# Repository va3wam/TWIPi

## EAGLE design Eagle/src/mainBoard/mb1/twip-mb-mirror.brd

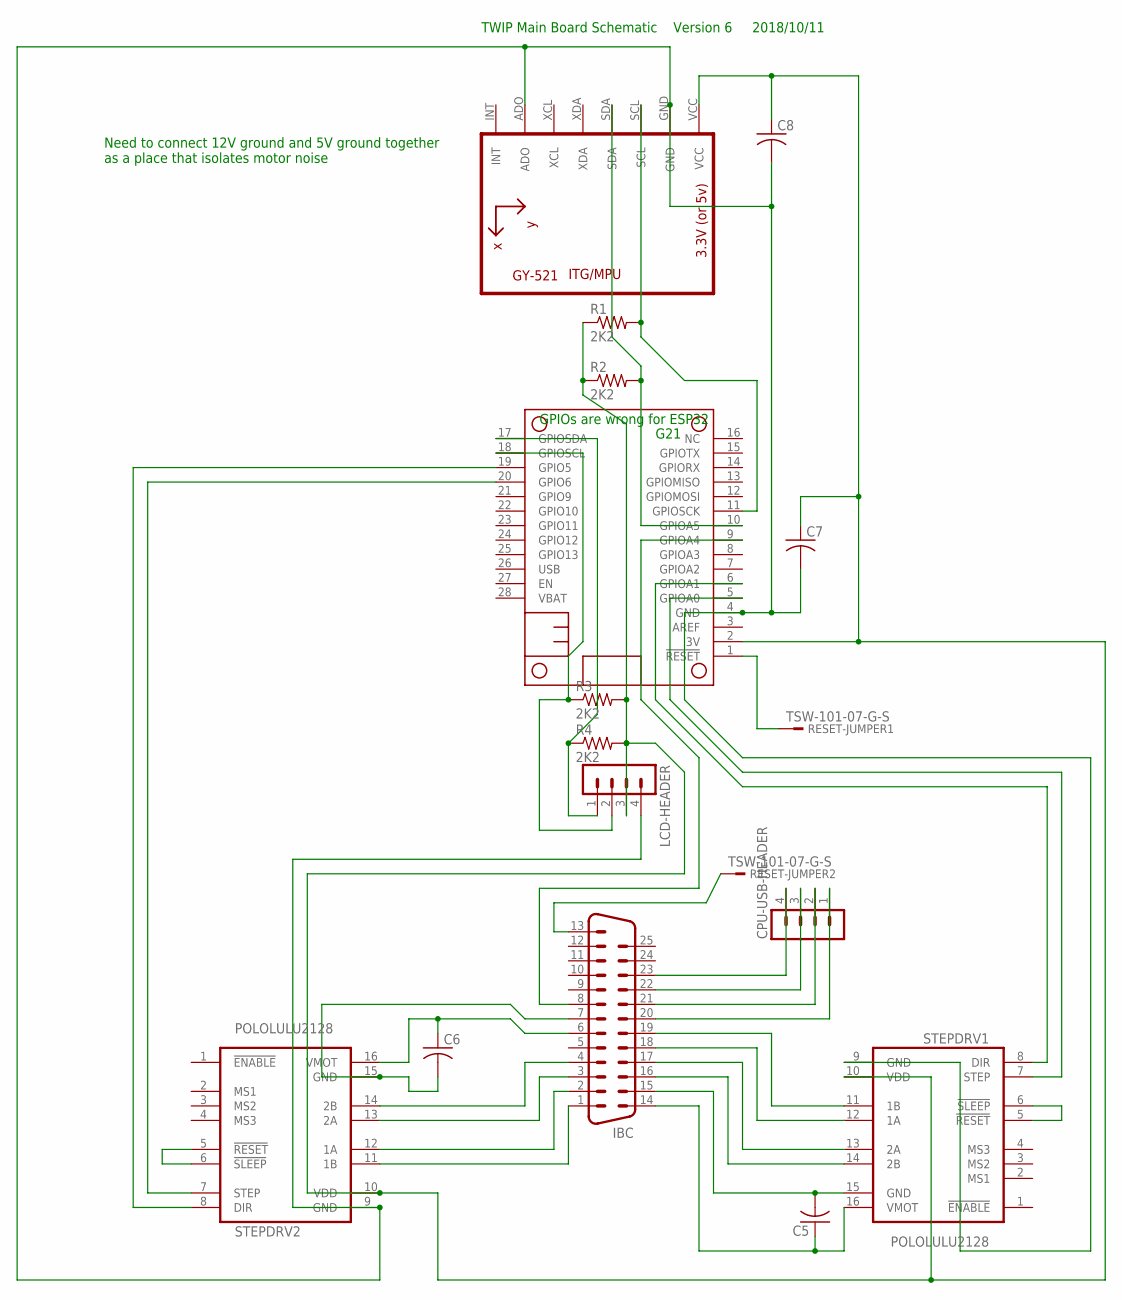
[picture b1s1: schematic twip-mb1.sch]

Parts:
C5, C6, C7, C8: C-US050-024X044; C050-024X044
CPU-USB-HEADER: MA04-1
IBC: M25VP
LCD-HEADER: MA04-1
MS2: FEATHERWING_NOHOLES
R1, R2, R3, R4: 2K2; 0309/12
RESET-JUMPER1, RESET-JUMPER2: TSW-101-07-G-S; TSW-101-XX-G-S
STEPDRV1, STEPDRV2: POLOLULU2128
U1: GY-521MPU6050; GY-521

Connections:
3V: C7.1, C8.1, LCD-HEADER.3, MS2.2 (3V), R1.1, R2.1, R3.2, R4.2, STEPDRV1.10 (VDD), STEPDRV2.10 (VDD), U1.VCC
unnamed: IBC.13, RESET-JUMPER2.1
unnamed: C6.2, IBC.7, STEPDRV2.15 (GND)
unnamed: IBC.16, STEPDRV1.14 (2B)
unnamed: IBC.17, STEPDRV1.13 (2A)
unnamed: MS2.5 (GPIOA0), STEPDRV1.7 (STEP)
unnamed: IBC.18, STEPDRV1.12 (1A)
unnamed: IBC.19, STEPDRV1.11 (1B)
unnamed: IBC.1, STEPDRV2.11 (1B)
unnamed: IBC.2, STEPDRV2.12 (1A)
unnamed: IBC.3, STEPDRV2.13 (2A)
unnamed: LCD-HEADER.2, MS2.18 (GPIOSCL), R3.1
unnamed: IBC.4, STEPDRV2.14 (2B)
unnamed: CPU-USB-HEADER.4, IBC.23
unnamed: CPU-USB-HEADER.3, IBC.22
unnamed: MS2.6 (GPIOA1), STEPDRV1.8 (DIR)
unnamed: MS2.1 (!RESET), RESET-JUMPER1.1
unnamed: MS2.11 (GPIOSCK), R1.2, U1.SCL
unnamed: CPU-USB-HEADER.2, IBC.21
unnamed: LCD-HEADER.1, MS2.17 (GPIOSDA), R4.1
unnamed: C5.2, IBC.15, STEPDRV1.15 (GND)
unnamed: C6.1, IBC.6, STEPDRV2.16 (VMOT)
unnamed: C5.1, IBC.14, STEPDRV1.16 (VMOT)
unnamed: STEPDRV1.5 (!RESET), STEPDRV1.6 (!SLEEP)
unnamed: STEPDRV2.5 (!RESET), STEPDRV2.6 (!SLEEP)
unnamed: MS2.10 (GPIOA5), R2.2, U1.SDA
unnamed: MS2.19 (GPIO5), STEPDRV2.8 (DIR)
unnamed: IBC.8, MS2.9 (GPIOA4)
unnamed: MS2.20 (GPIO6), STEPDRV2.7 (STEP)
unnamed: CPU-USB-HEADER.1, IBC.20
unnamed: C7.2, C8.2, LCD-HEADER.4, MS2.4 (GND), STEPDRV1.9 (GND), STEPDRV2.9 (GND), U1.ADO, U1.GND

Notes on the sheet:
GPIOs are wrong for ESP32
G21
Need to connect 12V ground and 5V ground together as a place that isolates motor noise
TWIP Main Board Schematic Version 6 2018/10/11

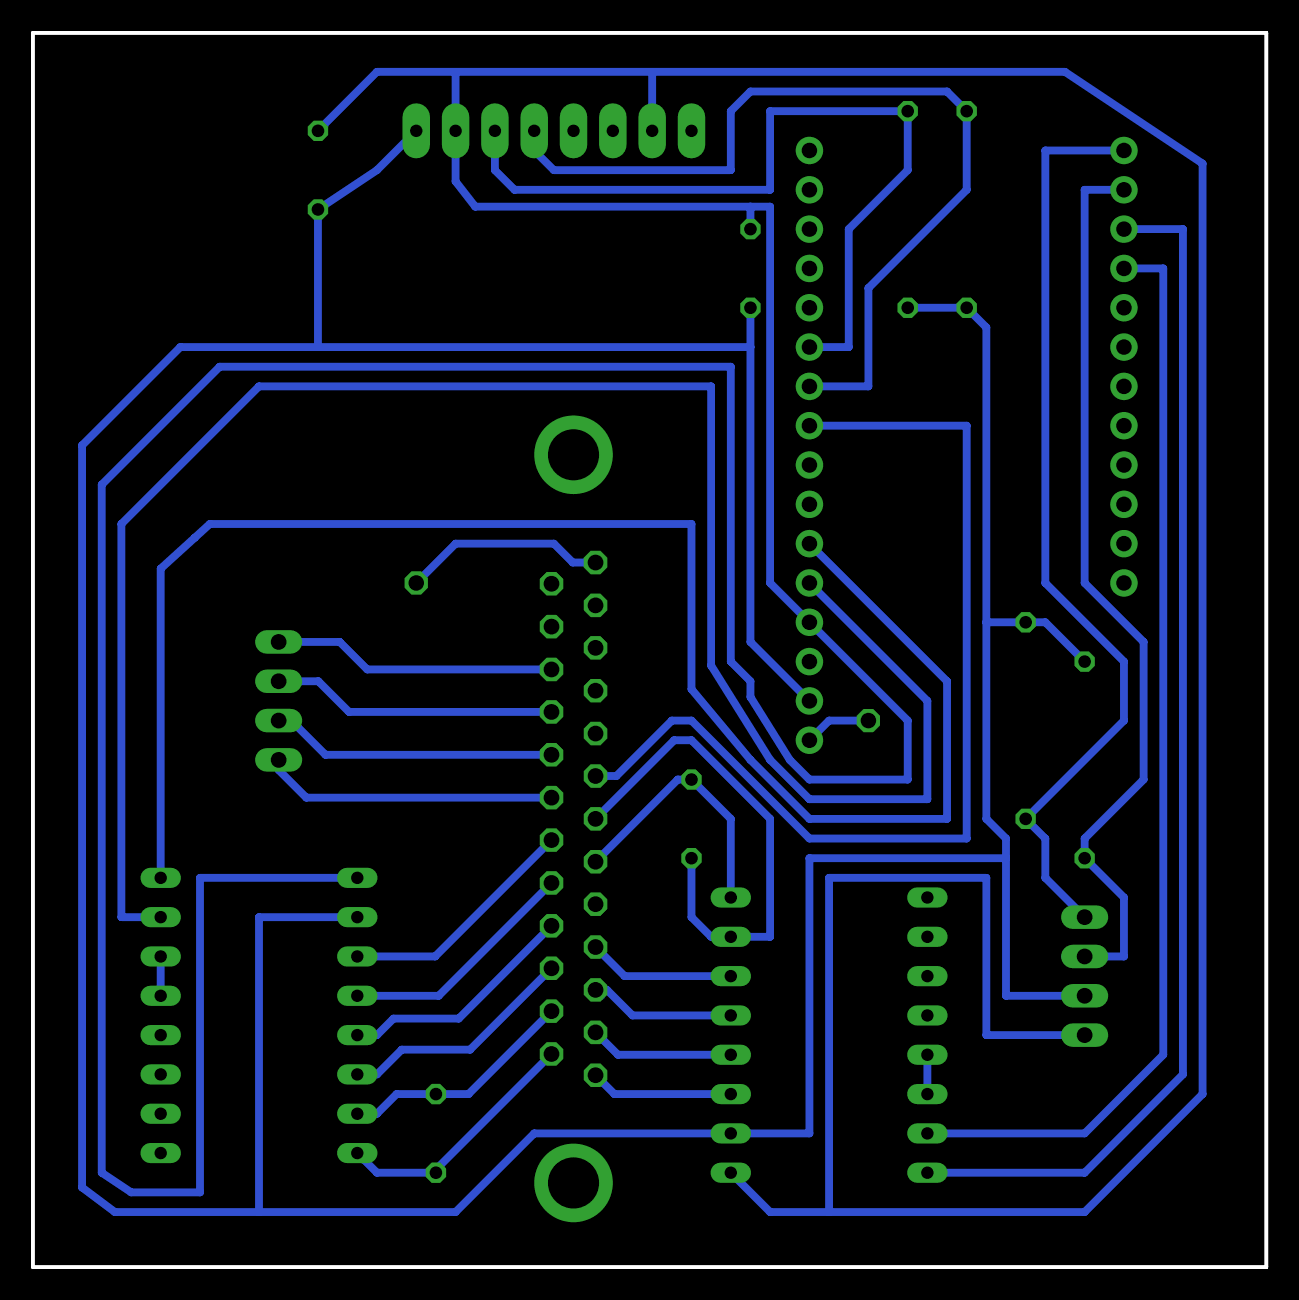
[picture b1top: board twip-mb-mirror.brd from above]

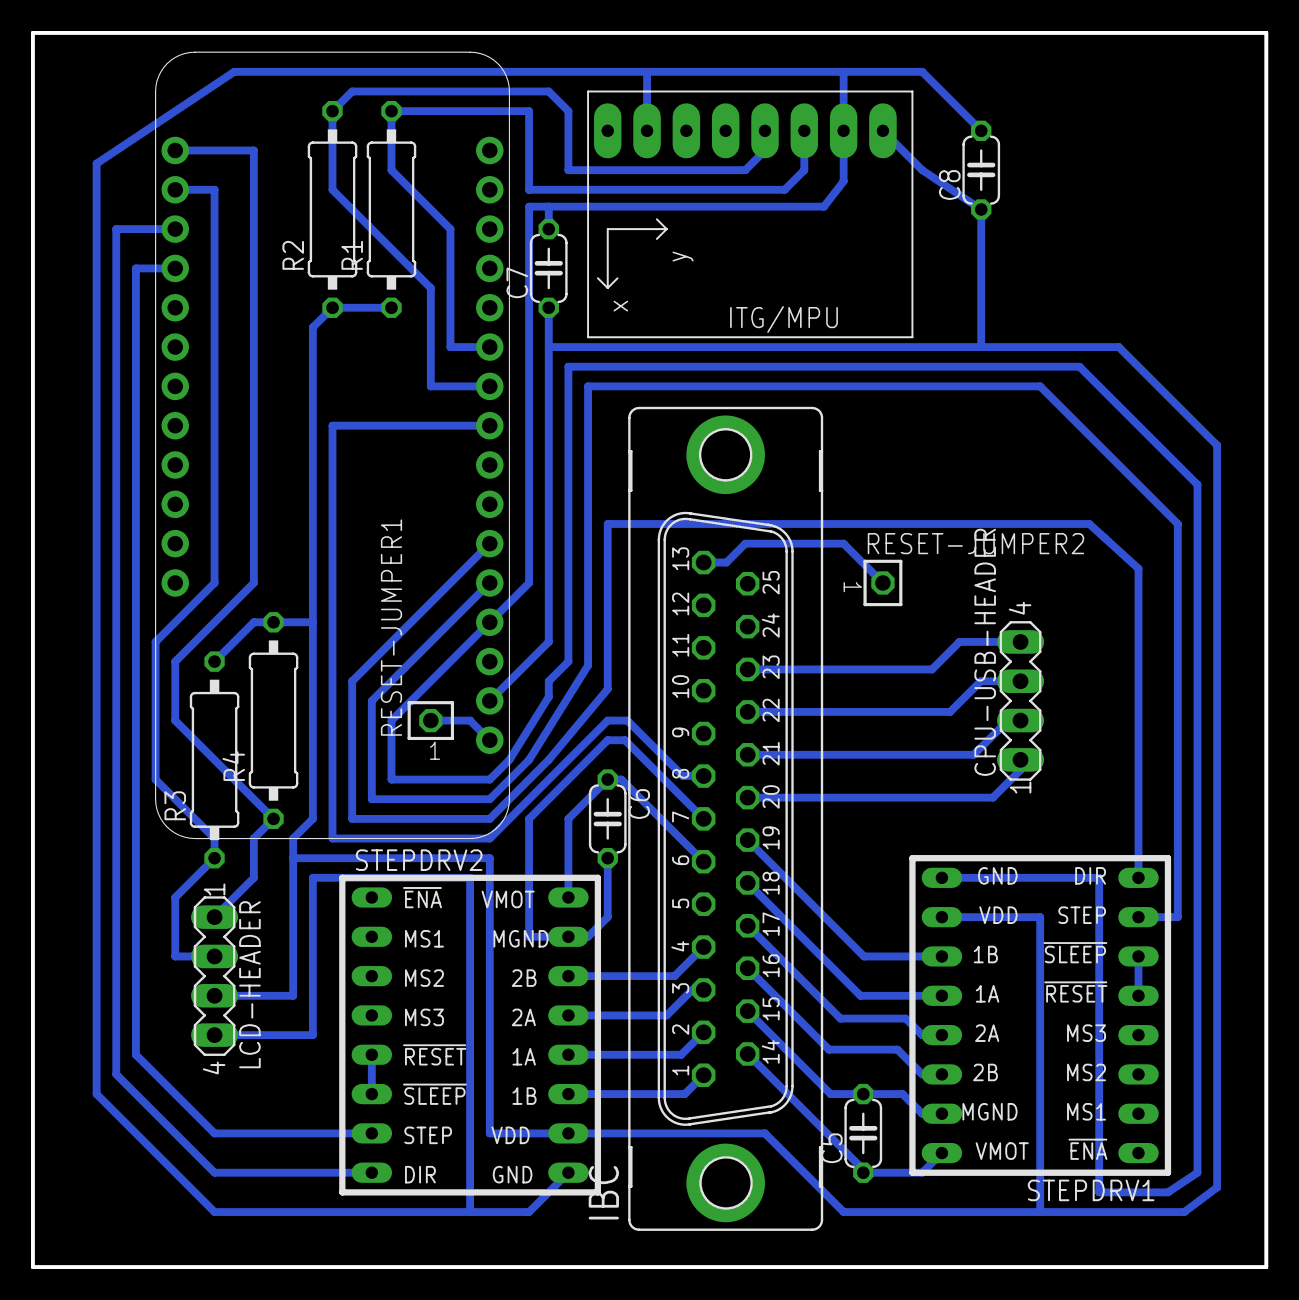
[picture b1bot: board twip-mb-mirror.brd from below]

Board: 2 copper layers, 79.7 x 79.7 mm, 17 parts (17 on the bottom side), 31 nets.

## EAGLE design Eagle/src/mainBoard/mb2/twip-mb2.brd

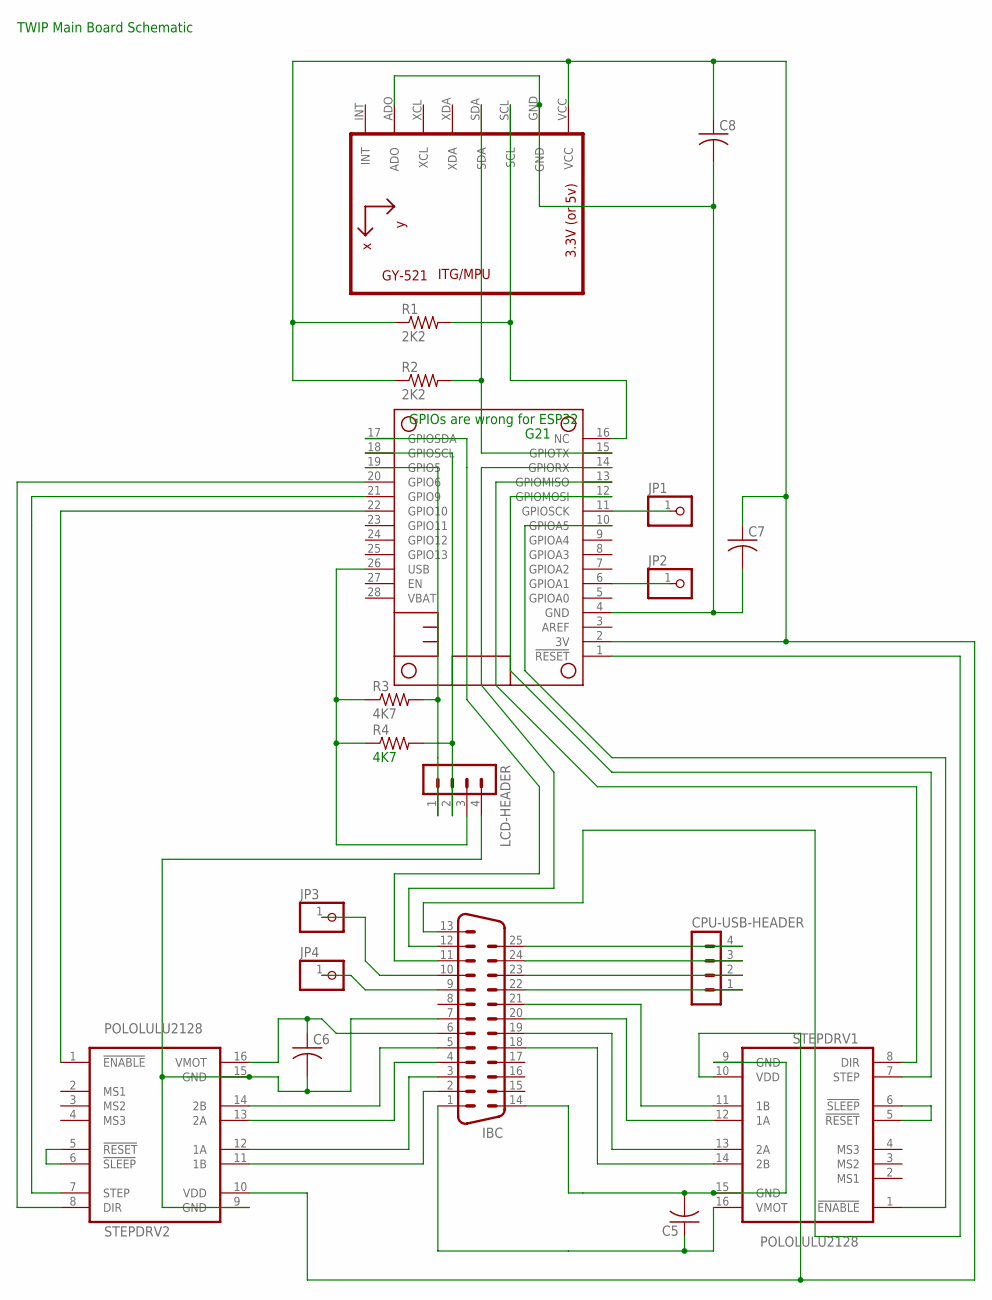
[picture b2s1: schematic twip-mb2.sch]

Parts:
C5, C6, C7, C8: C-US050-024X044; C050-024X044
CPU-USB-HEADER: MA04-1
IBC: M25VP
JP1, JP2, JP3, JP4: PINHD-1X1; 1X01
LCD-HEADER: MA04-1
MS2: FEATHERWING_NOHOLES
R1, R2: 2K2; 0309/12
R3, R4: 4K7; 0309/12
STEPDRV1, STEPDRV2: POLOLULU2128
U1: GY-521MPU6050; GY-521

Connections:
3V: C7.1, C8.1, MS2.2 (3V), R1.1, R2.1, STEPDRV1.10 (VDD), STEPDRV2.10 (VDD), U1.VCC
unnamed: C7.2, C8.2, MS2.4 (GND), U1.ADO, U1.GND
unnamed: IBC.18, STEPDRV1.14 (2B)
unnamed: IBC.19, STEPDRV1.13 (2A)
unnamed: MS2.12 (GPIOMOSI), STEPDRV1.7 (STEP)
unnamed: IBC.20, STEPDRV1.12 (1A)
unnamed: IBC.21, STEPDRV1.11 (1B)
unnamed: IBC.2, STEPDRV2.11 (1B)
unnamed: IBC.3, STEPDRV2.12 (1A)
unnamed: IBC.4, STEPDRV2.13 (2A)
unnamed: LCD-HEADER.1, MS2.19 (GPIO5), R3.2
unnamed: IBC.5, STEPDRV2.14 (2B)
unnamed: CPU-USB-HEADER.4, IBC.25
unnamed: CPU-USB-HEADER.3, IBC.24
unnamed: MS2.13 (GPIOMISO), STEPDRV1.8 (DIR)
unnamed: IBC.13, MS2.1 (!RESET)
unnamed: MS2.16 (NC), R1.2, U1.SCL
unnamed: CPU-USB-HEADER.2, IBC.23
unnamed: IBC.12, MS2.14 (GPIORX)
unnamed: C5.2, IBC.14, STEPDRV1.9 (GND), STEPDRV1.15 (GND)
unnamed: C6.1, IBC.6, STEPDRV2.16 (VMOT)
unnamed: C5.1, IBC.1, STEPDRV1.16 (VMOT)
unnamed: STEPDRV1.5 (!RESET), STEPDRV1.6 (!SLEEP)
unnamed: STEPDRV2.5 (!RESET), STEPDRV2.6 (!SLEEP)
unnamed: MS2.15 (GPIOTX), R2.2, U1.SDA
unnamed: MS2.20 (GPIO6), STEPDRV2.8 (DIR)
unnamed: IBC.11, MS2.17 (GPIOSDA)
unnamed: MS2.21 (GPIO9), STEPDRV2.7 (STEP)
unnamed: CPU-USB-HEADER.1, IBC.22
unnamed: MS2.10 (GPIOA5), STEPDRV1.1 (!ENABLE)
unnamed: JP1.1, MS2.11 (GPIOSCK)
unnamed: C6.2, IBC.7, LCD-HEADER.4, STEPDRV2.9 (GND), STEPDRV2.15 (GND)
unnamed: MS2.22 (GPIO10), STEPDRV2.1 (!ENABLE)
unnamed: LCD-HEADER.2, MS2.18 (GPIOSCL), R4.2
unnamed: JP2.1, MS2.6 (GPIOA1)
unnamed: IBC.10, JP3.1
unnamed: IBC.9, JP4.1
USB: LCD-HEADER.3, MS2.26 (USB), R3.1, R4.1

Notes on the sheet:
GPIOs are wrong for ESP32
G21
TWIP Main Board Schematic

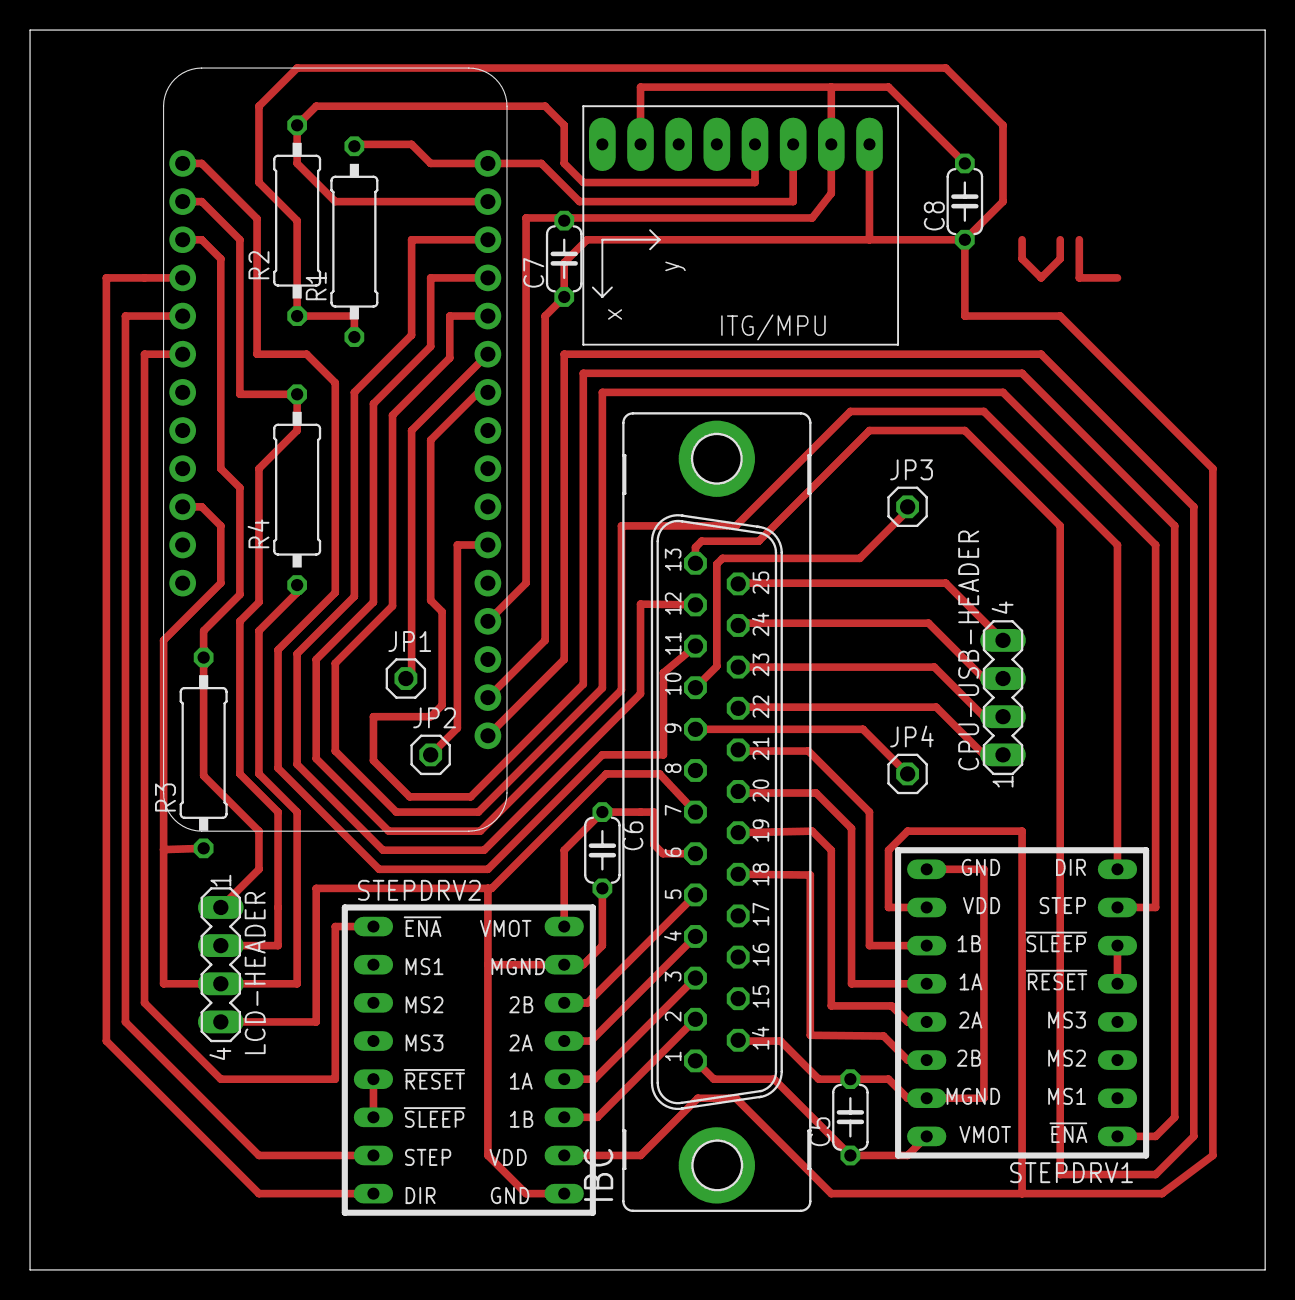
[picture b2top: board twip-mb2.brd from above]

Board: 2 copper layers, 82.2 x 82.5 mm, 19 parts (0 on the bottom side), 38 nets.

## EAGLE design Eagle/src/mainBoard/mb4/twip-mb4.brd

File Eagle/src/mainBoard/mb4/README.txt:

The MB4 and PB4 are based on the single board configuration being split in half.
TheRV8825's are moved and the coild headers are on the main board.
The interboard connector is a header with about 16 pins

You'll need to use PB4 with MB4 due to interconnection changes.

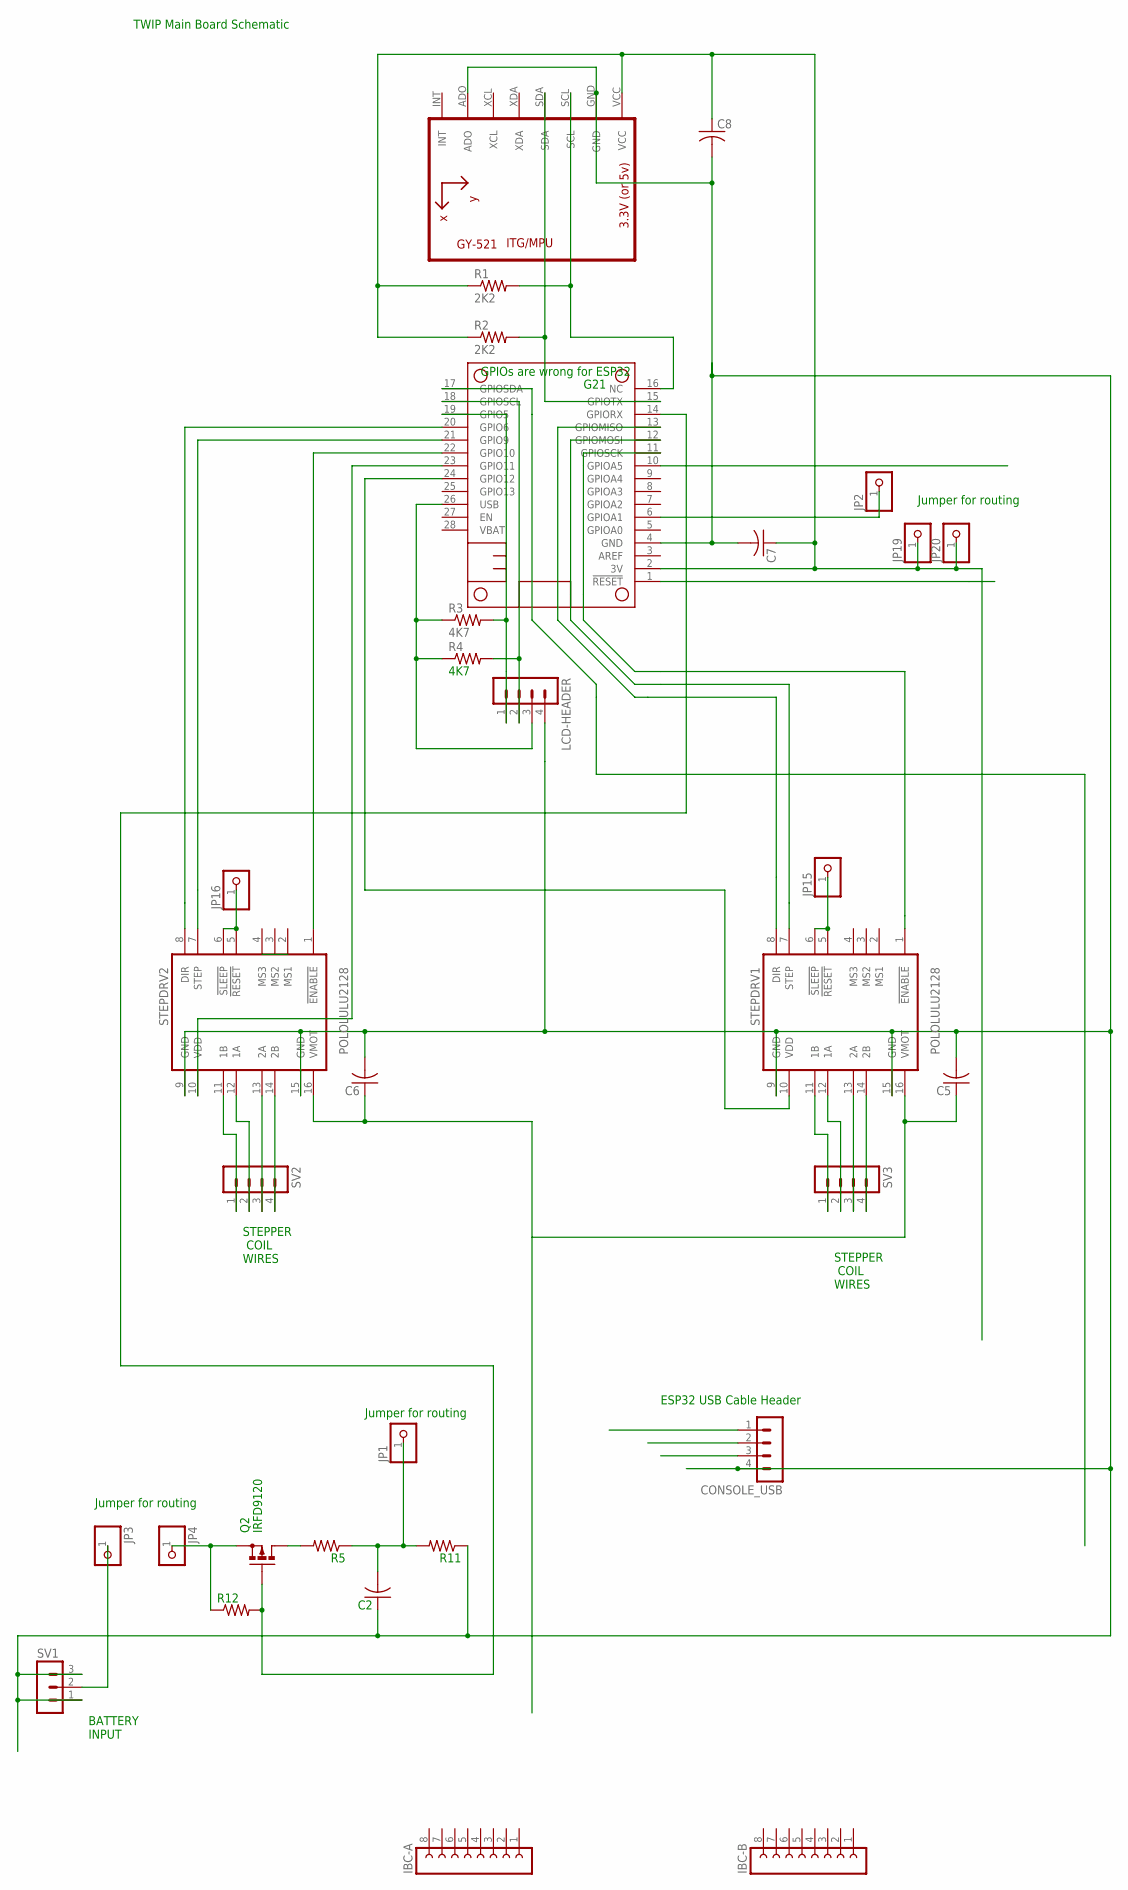
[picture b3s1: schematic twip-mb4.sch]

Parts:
C2: C-US050-025X075; C050-025X075
C5, C6, C7, C8: C-US050-024X044; C050-024X044
CONSOLE_USB: MA04-1
IBC-A: FE08-1; FE08
IBC-B: FE08-1; FE08
JP1, JP2, JP3, JP4, JP15, JP16, JP19, JP20: PINHD-1X1; 1X01
LCD-HEADER: MA04-1
MS2: FEATHERWING_NOHOLES
Q2: IRFD9120; C370-01
R1, R2: 2K2; 0309/12
R3, R4: 4K7; 0309/12
R5, R11, R12: R-US_0207/10; 0207/10
STEPDRV1, STEPDRV2: POLOLULU2128
SV1: MA03-1
SV2, SV3: MA04-1
U1: GY-521MPU6050; GY-521

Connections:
3V: C7.1, C8.1, JP19.1, JP20.1, MS2.2 (3V), R1.1, R2.1, U1.VCC
unnamed: C5.1, STEPDRV1.16 (VMOT)
unnamed: MS2.13 (GPIOMISO), STEPDRV1.8 (DIR)
unnamed: JP15.1, STEPDRV1.5 (!RESET), STEPDRV1.6 (!SLEEP)
unnamed: MS2.14 (GPIORX), Q2.G, R12.2
unnamed: JP16.1, STEPDRV2.5 (!RESET), STEPDRV2.6 (!SLEEP)
unnamed: STEPDRV2.14 (2B), SV2.4
unnamed: C2.1, C5.2, C6.2, C7.2, C8.2, CONSOLE_USB.4, LCD-HEADER.4, MS2.4 (GND), R11.1, STEPDRV1.9 (GND), STEPDRV1.15 (GND), STEPDRV2.9 (GND), STEPDRV2.15 (GND), SV1.1, SV1.3, U1.ADO, U1.GND
unnamed: LCD-HEADER.1, MS2.19 (GPIO5), R3.2
unnamed: STEPDRV2.13 (2A), SV2.3
unnamed: STEPDRV2.12 (1A), SV2.2
unnamed: STEPDRV2.11 (1B), SV2.1
unnamed: MS2.12 (GPIOMOSI), STEPDRV1.7 (STEP)
unnamed: STEPDRV1.14 (2B), SV3.4
unnamed: MS2.16 (NC), R1.2, U1.SCL
unnamed: STEPDRV1.13 (2A), SV3.3
unnamed: STEPDRV1.12 (1A), SV3.2
unnamed: STEPDRV1.11 (1B), SV3.1
unnamed: MS2.11 (GPIOSCK), STEPDRV1.1 (!ENABLE)
unnamed: JP4.1, Q2.S, R12.1
unnamed: MS2.15 (GPIOTX), R2.2, U1.SDA
unnamed: MS2.20 (GPIO6), STEPDRV2.8 (DIR)
unnamed: MS2.21 (GPIO9), STEPDRV2.7 (STEP)
unnamed: C2.2, JP1.1, R5.1, R11.2
unnamed: JP3.1, SV1.2
unnamed: JP2.1, MS2.6 (GPIOA1)
unnamed: MS2.22 (GPIO10), STEPDRV2.1 (!ENABLE)
unnamed: LCD-HEADER.2, MS2.18 (GPIOSCL), R4.2
unnamed: MS2.23 (GPIO11), STEPDRV2.10 (VDD)
unnamed: MS2.24 (GPIO12), STEPDRV1.10 (VDD)
unnamed: C6.1, STEPDRV2.16 (VMOT)
unnamed: Q2.D, Q2.D1 (D), R5.2
USB: LCD-HEADER.3, MS2.26 (USB), R3.1, R4.1

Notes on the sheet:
GPIOs are wrong for ESP32
G21
TWIP Main Board Schematic
BATTERY INPUT
STEPPER COIL WIRES
Jumper for routing
ESP32 USB Cable Header

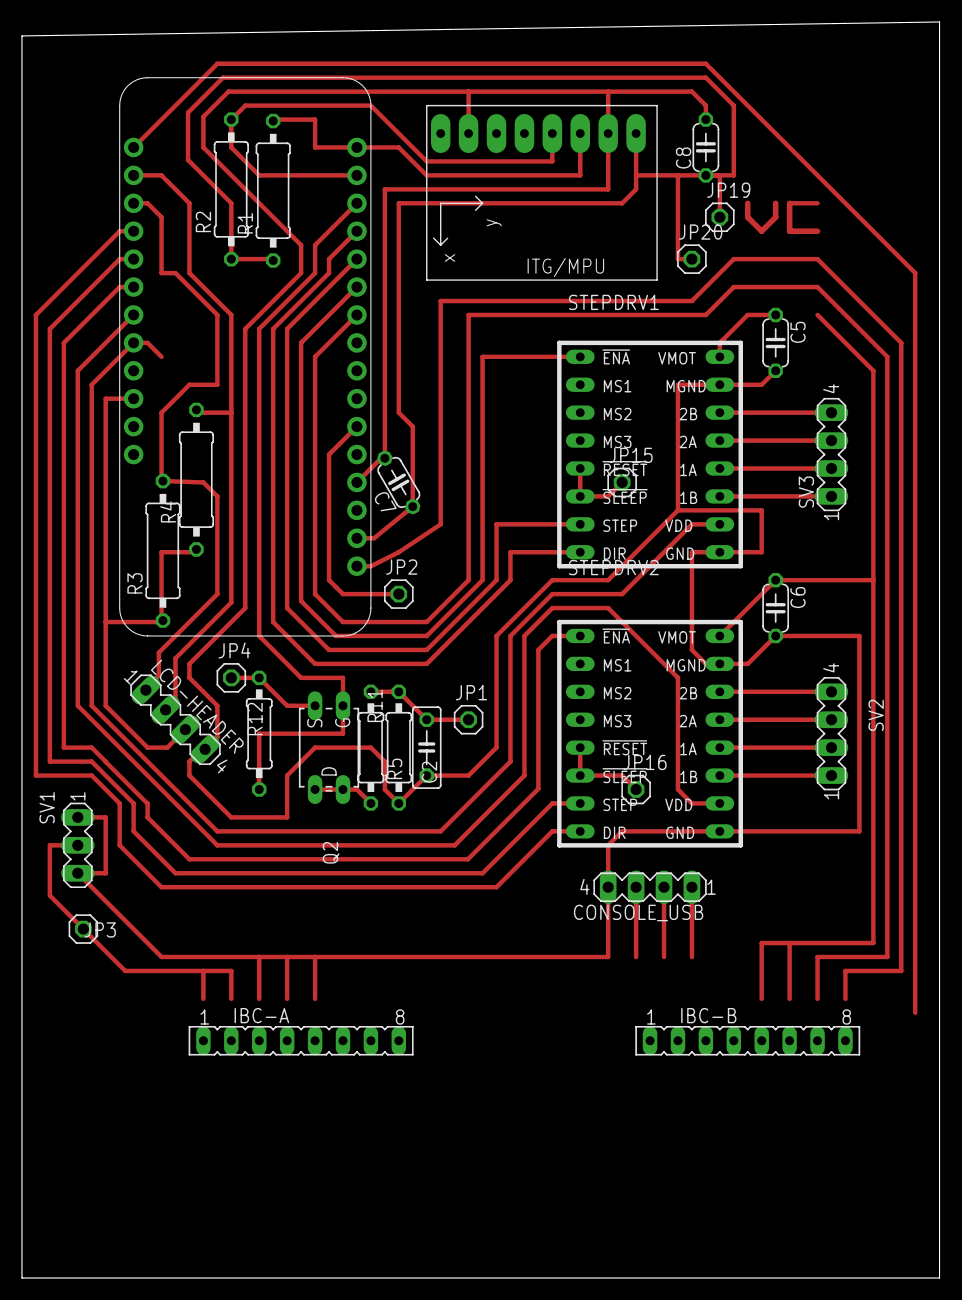
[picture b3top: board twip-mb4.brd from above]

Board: 2 copper layers, 83.5 x 114.3 mm, 32 parts (0 on the bottom side), 33 nets.
